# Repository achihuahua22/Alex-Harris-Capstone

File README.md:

# Alex Harris Capstone: Low Cost Device for Laboratory Equipment Integration
 _This project is a Raspberry Pi Hat that is intended to receive inputs from Self-Driving-Laboratory equipment and utilize the raspberry pi to publish device data onto the network.
This repository contains all of the schematics, documentation, and code necessary to build this device._

This project builds on an-ven’s [graspib](https://github.com/an-ven/graspib) project by adding more RS232 support and a UART breakout pin. 

It also utilizes the [Linux GPIB package](https://linux-gpib.sourceforge.io)

Currently, this device supports UART, RS232, and GPIB. 

If you want to make one yourself, the files are [here](capstone_cad_rev4)

## Introduction
This project is a Raspberry Pi Hat that is intended to 
improve self driving lab connectivity and modularity 
by allowing researchers to integrate multiple lab 
devices into their networks. I worked with Dr. Taylor 
Sparks' self-driving laboratory (SDL) to develop a 
device to more easily network with lab equipment. 
A self-driving laboratory is a laboratory where
everything from specimen handling, experiments, 
and decision making is fully automated to 
accelerate research [1]. This device intends to be an 
easy-to-use device for networking and save 
researchers money. To make a device “easy to use” I 
wanted to work with hardware that researchers are 
familiar with. This led to me choosing to design a 
board that attaches to a Raspberry Pi. 
I chose to use a Raspberry Pi based solution
because of its prevalence in the research space. 
Many pieces of university research level lab 
equipment have very little interconnection due to 
the age of the device or the type of communication 
protocol. Another issue is that products can use 
proprietary connection methods, which makes the 
task of developing an interconnected SDL very 
difficult [2]. I wanted to develop a device that can 
put data collected by lab equipment onto the 
network using a Raspberry Pi and a circuit board 
that sits on top of the Pi to handle the 
communications.

## Design
### Methods
I began with researching similar solutions to this 
problem, and the two options were a series of adapter 
dongles, or a device that interfaces with a single board 
computer to allow for communication. I chose this 
method as it would be easiest for the end user to have a 
single device that handles lab equipment connectivity.
I started by purchasing pre-built adapter components 
and build a breadboard analog of the final device. This 
device consisted of RS232 adapters and a serial 
expansion board for a Raspberry Pi. With this, I was able 
to test the idea of sending device data over the network 
using ROS and the python socket library.

### Results
I designed a circuit board that could serve as an add on 
that connected to the Raspberry Pi’s GPIO port. To 
expand the capability of the device, a GPIB connection
was added, taking advantage of the open-source Linux 
GPIB package [3]. GPIB is a very common protocol with 
adapters often costing hundreds of dollars.
The board was manufactured by JLCPCB, hand 
assembled, revised, and tested thoroughly. A GitHub 
repository was maintained throughout the project 
detailing hardware and software setup instructions.
The low-cost goal was achieved with the total cost being 
around $40 for the entire device excluding shipping

### Conclusions
Improvements of the Linux GPIB library are needed to 
facilitate easy setup of hardware and improved 
compatibility with the IEEE-488 standard.
Future works should expand on the software for using 
the Raspberry Pi to communicate over the local 
network. Possibly a user interface to improve ease of 
use
Future works should also investigate more permanent, 
universal communication protocols to improve 
laboratory equipment integration.

### Communication Protocols
While there are many communication protocols used in laboratory equipment, a few come up most often when looking at the back of devices in labs around my university. Some of these include:

1. RS232
2. CAN (CAN-FD, etc.)
3. GPIB
4. USB
5. UART
6. HPIB
7. Ethernet

Obviously, it is not possible to develop a device to encompass every existing communication protocol, so I chose three that were most necessary to our SDL and were most feasible with the constraint of a Raspberry Pi powered device. The three protocols I chose were RS232, UART, and GPIB. I chose each of these for the following reasons:
#### _UART_
I chose UART because of its prevalence in open-source projects such as the OpenTrickler, a powder dispensing device that we are using in our SDL. UART is also a simple protocol to implement as it only requires four pins: 3v3, TX, RX, and GND. The end user can configure the Baud rate, parity or stop bits in software. I believe that including this communication allows for other SDLs to integrate their own custom devices and not have to design for network capabilities if they choose to use my device. 
#### _RS232_
I chose RS232 because it was very prevalent in older equipment in our lab such as the Fischer Scientific Analytical Scale, and some open-source devices such as the OpenRAMAN, a laser spectroscopy device for materials classification. While RS232 is an old communication protocol, it is still useful for simple communication of commands. 
#### _GPIB_
Lastly, I chose GPIB because it was also extremely prevalent in many types of laboratory equipment such as multimeters, spectrum analyzers, and other devices. The issue that many laboratories face with GPIB enabled devices is that adapters such as GPIB to USB can cost more than $1,000 and can only communicate with proprietary software. This can render perfectly usable lab equipment almost completely useless in terms of automation or remote data collection.

The following are protocols I didn't choose, future works could consider adding them.

#### _CAN_
I didn’t choose CAN or any of its variants (CAN, CAN-FD, CAN-XL) because it has too many variants to effectively develop a multipurpose product that could encompass of CAN. The differential pair nature of CAN also makes it difficult to develop for.
#### _USB_
I didn’t choose USB because of its complication with drivers, enumeration, host/peripheral, and all the headaches that come with that. In addition to this, a Raspberry Pi does not have the same driver setup as a normal computer which makes implementation difficult when this problem can be solved with a computer and a USB hub.
#### _HPIB_
I didn’t choose HPIB because of the general nature of GPIB (General Purpose Interface Bus) and how HPIB is limited to Hewlett-Packard devices, and that does not make sense with the intent of this project.
#### _Ethernet_
I didn’t choose Ethernet because it also defeats the purpose of this project. The Raspberry Pi used for this project has Ethernet connection capabilities, allowing me to develop a device that just handles the communications between the laboratory equipment and the Pi, reducing cost and complexity.

## Device Assembly
### PCB Manufacturing
At the time of writing, JLCPCB is a very good option for low cost PCB manufacturing. You can get 5 boards for roughly $4 not including shipping. All you need to do is zip these [Gerber Files](https://github.com/achihuahua22/Alex-Harris-Capstone/tree/main/capstone_rev4_gerbers), go to JLCPCB.com, click "upload gerbers" and choose the zipped file. Everything else should populate automatically. You don't need to do any configuration besides choosing the "Lead Free HASL" for a lead free surface finish on the pcb. Feel free to order a stencil as it might make surface mount soldering easier, not required though.

### Parts
Here is the [BOM](https://github.com/achihuahua22/Alex-Harris-Capstone/blob/main/bill_of_materials/senior_capstone_bom_rev4.csv) for the pcb components
   - Unfortunately, all of the components except for item 15 (SN75161BDW) can be purchased from Digikey, the remaining component can be purchased from Mouser
   - In addition, I would recommend M2.5 standoffs to support the board on top of the raspberry pi
   - Solder paste and Heat Gun is recommended for the Surface Mount components as the Resistors, Capacitors, and LED's

### Building
I would recommend using solder paste and a heat gun for installing the small surface mount components such as the resistors, capacitors, crystal and LED's and installing the components in the following order:
1. Resistors (R1-R12)
2. Crystal Oscillator (Y1)
3. Capacitors (C1-C8)
4. LED's (D1-D7) (*pay attention to the orientation of the LED!*)
   - The open part of the rectangle is the anode, the closed part is the cathode
5. Integrated Circuits (U1-U4) (In order of 1 to 4 is easiest)
6. Connectors

It is not required to install the components in this order, but is is easier to install the smaller components first so you don't have to navigate around the large connectors or IC's.
   
## Setup
1. Setup fresh install of [raspberry pi os](https://www.raspberrypi.com/software/)
2. Configure your network, password, etc to your liking
3. Download Provided [files](https://github.com/achihuahua22/Alex-Harris-Capstone/blob/main/send_to_network.c) to send data to network
4. From [graspib documentation](https://github.com/an-ven/graspib/tree/main) : 

   Install build tools and dependencies
   - Build tools: ```$ sudo apt install build-essential autoconf automake libtool flex bison```
   - RPi kernel headers: ```$ sudo apt install raspberrypi-kernel-headers```
   - Python3 headers: ```$ sudo apt install python3-dev```

    Download linux-gpib source files
   - Get release archives (4.3.4 or later) from https://sourceforge.net/projects/linux-gpib/files
   - or get the latest source from https://sourceforge.net/p/linux-gpib/code/HEAD/tree/

   Build and install kernel drivers
   - Enter linux-gpib-kernel directory ```$ cd linux-gpib-src-dir/linux-gpib-kernel```
   - Build kernel module by running make ```$ make```
   - Install kernel module ```$ sudo make install```
   - Update kernel module list ```$ sudo depmod -a```
   - Load gpib_bitbang kernel module ```$ sudo modprobe gpib_bitbang```
   - Now there should be some gpib* devices in /dev
   - Make the module loads on boot by adding gpib_bitbang line to /etc/modules-load.d/modules.conf

   When Raspberry Pi OS kernel gets upgraded, linux-gpib kernel module also needs to be rebuilt and reinstalled. 
   Basically just repeat above make and make install steps when kernel gets upgraded

   Build and install user space tools
   - Enter linux-gpib-user directory: ```$ cd linux-gpib-src-dir/linux-gpib-user```
   - If building from svn checkout first run bootstrap script: $ ./bootstrap
   - Run configure script: ```$ ./configure (run $ ./configure --help to list additional options)```
   - Build user space tools by running make: $ make
   - Install user space tools: ```$ sudo make install```
   - Make sure that shared library directory (default: /usr/local/lib/) is listed in: /etc/ld.so.conf.d/
   - Then run: $ sudo ldconfig

   Configure GPIB interface
   - Open gpib.conf configuration file $ sudo nano /usr/local/etc/gpib.conf (default location)
   - Set board_type = "gpib_bitbang" and other relevant settings (for details refer to included gpib.conf file, linux-gpib documentetion and included template file linux-gpib-src-dir/linux-gpib-user/util/template/gpib.conf)
   - Run gpib_config so the driver reads the configuration file $ sudo gpib_config --minor 0
   - Make the last command execute on every startup using crontab entry:
   - Edit crontab for root user: ```$ sudo crontab -e```
   - Add line the following line to cron tab file: @reboot /usr/local/sbin/gpib_config --minor 0
   - Enable non root users to use GPIB interface without sudo
   - Add new gpib system group: ```$ sudo groupadd -r gpib```
   - Append your_user_name to gpib supplementary group: ```$ sudo usermod -a -G gpib your_user_name```
   - Create /etc/udev/rules.d/99-gpib.rules file and add line: SUBSYSTEM=="gpib_common", GROUP="gpib", MODE="0660"

Reboot system to apply changes (udevadm utility can also be used, but reboot is dead simple to remember)
Test by running ibtest without sudo

5. Run and do the following to enable the I2C interface:
   - Open a terminal and run ```sudo raspi-config```
   - Select "Interface Options"
   - Select "P5 I2C"
   - It will prompt you with "Would you like the ARM I2C interface to be enabled?" *select yes*
   - Then it will prompt you to reboot *select yes*
   - After reboot, open another terminal and run ```sudo apt-get update``` and ```sudo apt-get install -y python3-smbus i2c-tools```
   - Finally shut down the raspberry pi with ```sudo halt```
   - Wait 10 seconds unplug power and restart
6. Run the following in the raspberry pi os terminal to configure serial and socket:
   
   - Update package list ```sudo apt update```
   - Install socket ```python3 -m pip install socket```
   - Install pySerial ```python3 -m pip install pyserial```
   - Install WiringPi ```sudo apt install wiringpi```
   - Install build tools ```sudo apt install build-essential```

7. See following [instructions](https://github.com/an-ven/graspib/tree/main) from grasPIB repository to configure the raspberry pi for GPIB
8. Configure Baud rate, IP, and I2C addresses in code

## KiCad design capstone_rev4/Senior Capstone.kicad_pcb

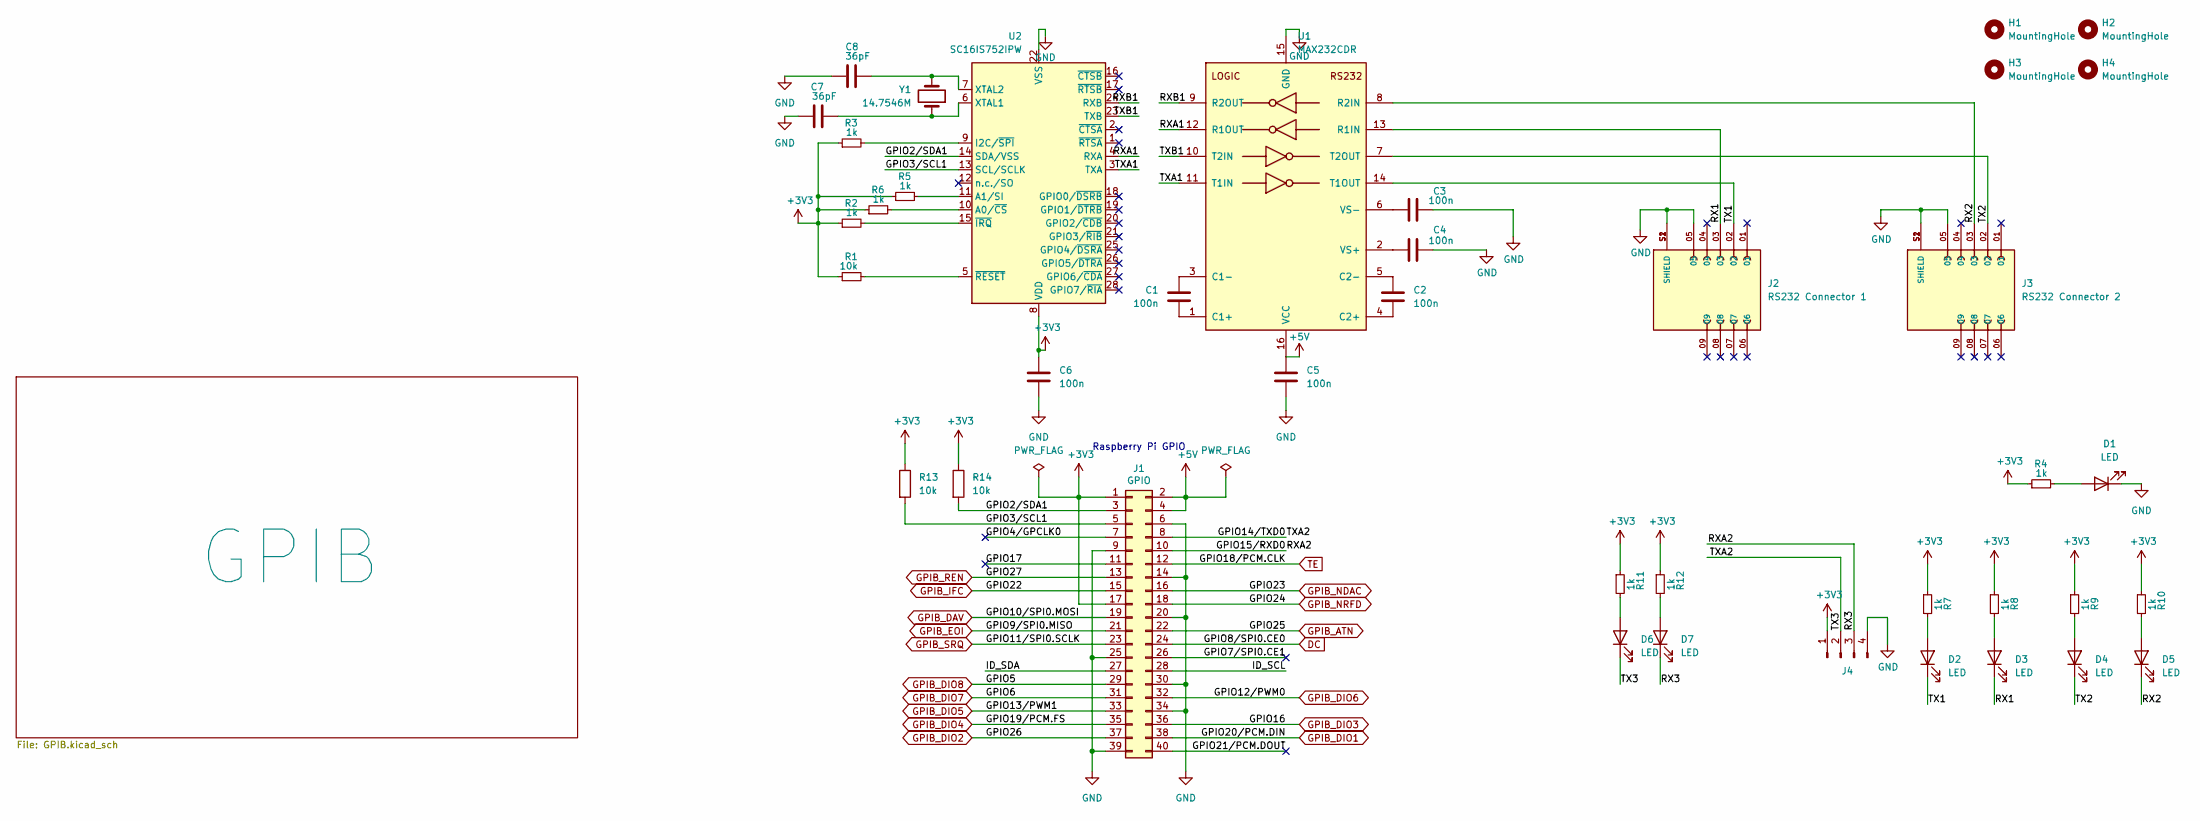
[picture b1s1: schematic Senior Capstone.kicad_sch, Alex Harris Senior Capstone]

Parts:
C1, C2, C3, C4, C5, C6: 100n; C_0805_2012Metric
C7, C8: 36pF; C_0805_2012Metric_Pad1.18x1.45mm_HandSolder
D1, D2, D3, D4, D5, D6, D7: LED; LED_1206_3216Metric_Pad1.42x1.75mm_HandSolder
H1, H2, H3, H4: MountingHole; MountingHole_2.7mm_M2.5_DIN965_Pad_TopBottom
J1: GPIO; PinSocket_2x20_P2.54mm_Vertical
J2: RS232 Connector 1; AMPHENOL_L77SDE09SA4CH3FC309; PARTREV 1
J3: RS232 Connector 2; AMPHENOL_L77SDE09SA4CH3FC309; PARTREV 1
J4: Conn_01x04_Pin; PinHeader_1x04_P2.54mm_Vertical
R1, R13, R14: 10k; R_0805_2012Metric_Pad1.20x1.40mm_HandSolder
R2, R3, R4, R5, R6, R7, R8, R9, R10, R11, R12: 1k; R_0805_2012Metric_Pad1.20x1.40mm_HandSolder
U1: MAX232CDR; SOIC-16_3.9x9.9mm_P1.27mm
U2: SC16IS752IPW; TSSOP-28_4.4x9.7mm_P0.65mm
Y1: 14.7546M; XTAL_405C35B14M74560

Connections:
+3V3: C6.1, J1.1, J1.17, J4.1, R1.1, R2.1, R3.1, R4.1, R5.1, R6.1, R7.1, R8.1, R9.1, R10.1, R11.1, R12.1, R13.1, R14.1, U2.8 (VDD)
+5V: C5.1, J1.2, J1.4, U1.16 (VCC); also elsewhere on the board
/GPIO2/SDA1: J1.3, R14.2, U2.14 (SDA/VSS)
/GPIO3/SCL1: J1.5, R13.2, U2.13 (SCL/SCLK)
/GPIO4/GPCLK0: J1.7
/GPIO7/SPI0.CE1: J1.26
/GPIO14/TXD0: D6.1 (K), J1.8, J4.2
/GPIO15/RXD0: D7.1 (K), J1.10, J4.3
/GPIO17: J1.11
/GPIO21/PCM.DOUT: J1.40
/ID_SCL: J1.28
/ID_SDA: J1.27
/RX1: D3.1 (K), J2.03, U1.13 (R1IN)
/RX2: D5.1 (K), J3.03, U1.8 (R2IN)
/RXA1: U1.12 (R1OUT), U2.4 (RXA)
/RXB1: U1.9 (R2OUT), U2.24 (RXB)
/TX1: D2.1 (K), J2.02, U1.14 (T1OUT)
/TX2: D4.1 (K), J3.02, U1.7 (T2OUT)
/TXA1: U1.11 (T1IN), U2.3 (TXA)
/TXB1: U1.10 (T2IN), U2.23 (TXB)
DC: J1.24; also elsewhere on the board
GND: C3.2, C4.2, C5.2, C6.2, C7.2, C8.2, D1.1 (K), J1.6, J1.9, J1.14, J1.20, J1.25, J1.30, J1.34, J1.39, J2.05, J2.S1 (SHIELD), J2.S2 (SHIELD), J3.05, J3.S1 (SHIELD), J3.S2 (SHIELD), J4.4, U1.15 (GND), U2.22 (VSS); also elsewhere on the board
GPIB_ATN: J1.22; also elsewhere on the board
GPIB_DAV: J1.19; also elsewhere on the board
GPIB_DIO1: J1.38; also elsewhere on the board
GPIB_DIO2: J1.37; also elsewhere on the board
GPIB_DIO3: J1.36; also elsewhere on the board
GPIB_DIO4: J1.35; also elsewhere on the board
GPIB_DIO5: J1.33; also elsewhere on the board
GPIB_DIO6: J1.32; also elsewhere on the board
GPIB_DIO7: J1.31; also elsewhere on the board
GPIB_DIO8: J1.29; also elsewhere on the board
GPIB_EOI: J1.21; also elsewhere on the board
GPIB_IFC: J1.15; also elsewhere on the board
GPIB_NDAC: J1.16; also elsewhere on the board
GPIB_NRFD: J1.18; also elsewhere on the board
GPIB_REN: J1.13; also elsewhere on the board
GPIB_SRQ: J1.23; also elsewhere on the board
unnamed: D1.2 (A), R4.2
unnamed: D2.2 (A), R7.2
unnamed: D3.2 (A), R8.2
unnamed: D4.2 (A), R9.2
unnamed: D5.2 (A), R10.2
unnamed: D6.2 (A), R11.2
unnamed: D7.2 (A), R12.2
unnamed: C1.2, U1.1 (C1+)
unnamed: C1.1, U1.3 (C1-)
unnamed: C2.2, U1.4 (C2+)
unnamed: C2.1, U1.5 (C2-)
unnamed: C4.1, U1.2 (VS+)
unnamed: C3.1, U1.6 (VS-)
unnamed: R6.2, U2.10 (A0/~CS)
unnamed: R5.2, U2.11 (A1/SI)
unnamed: R3.2, U2.9 (I2C/~SPI)
unnamed: C7.1, U2.6 (XTAL1), Y1.1
unnamed: C8.1, U2.7 (XTAL2), Y1.2
unnamed: R2.2, U2.15 (~IRQ)
unnamed: R1.2, U2.5 (~RESET)
TE: J1.12; also elsewhere on the board

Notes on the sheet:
Raspberry Pi GPIO

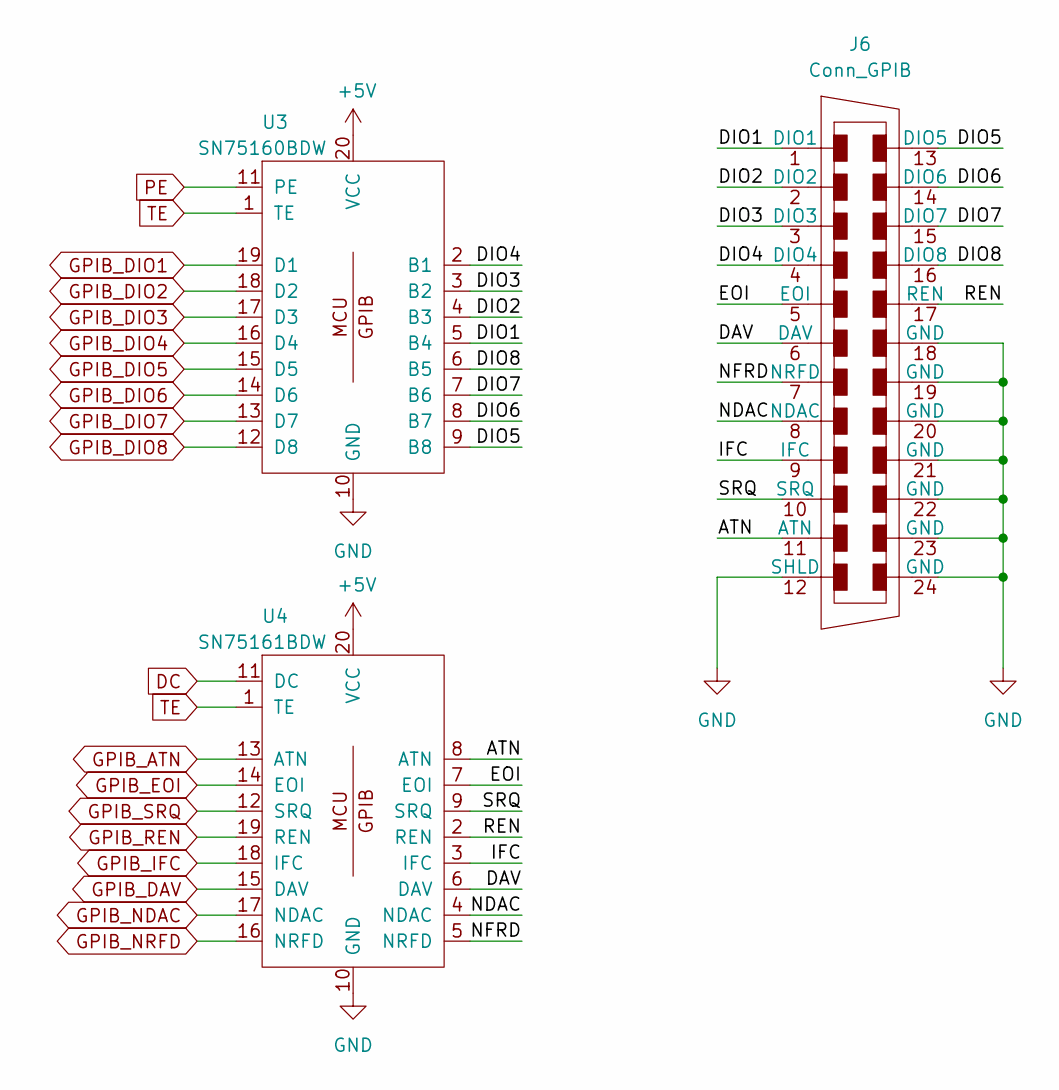
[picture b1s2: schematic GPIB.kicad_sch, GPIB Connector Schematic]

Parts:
J6: Conn_GPIB; CONN_112-024-113R001_NRC
U3: SN75160BDW; SOIC127P1030X265-20N
U4: SN75161BDW; SOIC127P1030X265-20N

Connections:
+5V: U3.20 (VCC), U4.20 (VCC); also elsewhere on the board
/GPIB/ATN: J6.11 (ATN), U4.8 (ATN)
/GPIB/DAV: J6.6 (DAV), U4.6 (DAV)
/GPIB/DIO1: J6.1 (DIO1), U3.5 (B4)
/GPIB/DIO2: J6.2 (DIO2), U3.4 (B3)
/GPIB/DIO3: J6.3 (DIO3), U3.3 (B2)
/GPIB/DIO4: J6.4 (DIO4), U3.2 (B1)
/GPIB/DIO5: J6.13 (DIO5), U3.9 (B8)
/GPIB/DIO6: J6.14 (DIO6), U3.8 (B7)
/GPIB/DIO7: J6.15 (DIO7), U3.7 (B6)
/GPIB/DIO8: J6.16 (DIO8), U3.6 (B5)
/GPIB/EOI: J6.5 (EOI), U4.7 (EOI)
/GPIB/IFC: J6.9 (IFC), U4.3 (IFC)
/GPIB/NDAC: J6.8 (NDAC), U4.4 (NDAC)
/GPIB/NFRD: J6.7 (NRFD), U4.5 (NRFD)
/GPIB/REN: J6.17 (REN), U4.2 (REN)
/GPIB/SRQ: J6.10 (SRQ), U4.9 (SRQ)
DC: U4.11 (DC); also elsewhere on the board
GND: J6.12 (SHLD), J6.18 (GND), J6.19 (GND), J6.20 (GND), J6.21 (GND), J6.22 (GND), J6.23 (GND), J6.24 (GND), U3.10 (GND), U4.10 (GND); also elsewhere on the board
GPIB_ATN: U4.13 (ATN); also elsewhere on the board
GPIB_DAV: U4.15 (DAV); also elsewhere on the board
GPIB_DIO1: U3.19 (D1); also elsewhere on the board
GPIB_DIO2: U3.18 (D2); also elsewhere on the board
GPIB_DIO3: U3.17 (D3); also elsewhere on the board
GPIB_DIO4: U3.16 (D4); also elsewhere on the board
GPIB_DIO5: U3.15 (D5); also elsewhere on the board
GPIB_DIO6: U3.14 (D6); also elsewhere on the board
GPIB_DIO7: U3.13 (D7); also elsewhere on the board
GPIB_DIO8: U3.12 (D8); also elsewhere on the board
GPIB_EOI: U4.14 (EOI); also elsewhere on the board
GPIB_IFC: U4.18 (IFC); also elsewhere on the board
GPIB_NDAC: U4.17 (NDAC); also elsewhere on the board
GPIB_NRFD: U4.16 (NRFD); also elsewhere on the board
GPIB_REN: U4.19 (REN); also elsewhere on the board
GPIB_SRQ: U4.12 (SRQ); also elsewhere on the board
PE: U3.11 (PE)
TE: U3.1 (TE), U4.1 (TE); also elsewhere on the board

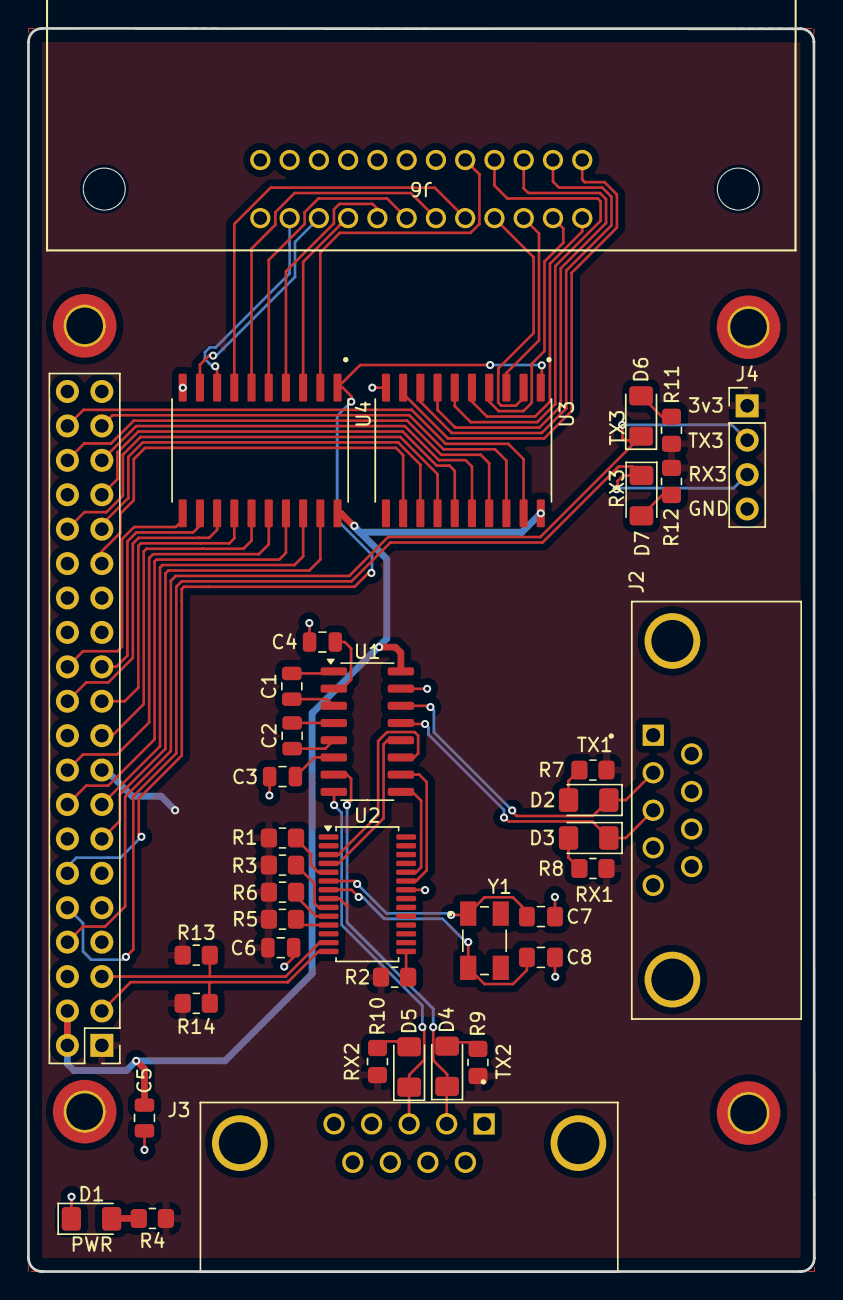
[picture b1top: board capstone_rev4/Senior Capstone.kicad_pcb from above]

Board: 2 copper layers, 58.0 x 91.8 mm, 43 parts (0 on the bottom side), 69 nets.

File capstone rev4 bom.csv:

Index,Manufacturer Part Number,Manufacturer Name,Description,References,Requested Quantity 1,Pack Quantity 1,Pack Type 1,Digi-Key Part Number 1,Unit Price 1,Extended Price 1,Minimum Order Quantity 1,Datasheet,Product Notes
1,22284040,Molex,CONN HEADER VERT 4POS 2.54MM,J4,1,1,Bulk,WM50014-04-ND,0.3,$0.30 ,1,https://www.molex.com/pdm_docs/sd/022284040_sd.pdf,
2,RC0805FR-071KL,YAGEO,RES 1K OHM 1% 1/8W 0805,"R2, R3, R4, R5, R6, R7, R8, R9, R10, R11, R12",11,11,Cut Tape (CT),311-1.00KCRCT-ND,0.012,$0.13 ,1,https://www.yageo.com/upload/media/product/products/datashee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,
3,08055C104J4T2A,KYOCERA AVX,CAP CER 0.1UF 50V X7R 0805,C1-C6,7,7,Cut Tape (CT),478-KAM21BR71H104JTCT-ND,0.18,$1.26 ,1,https://datasheets.kyocera-avx.com/AutoMLCC.pdf,
4,"SC16IS752IPW,112",NXP USA Inc.,IC UART DUAL 12C/SPI 28TSSOP,U2,1,1,Tube,568-4016-5-ND,4.48,$4.48 ,1,https://www.nxp.com/docs/en/data-sheet/SC16IS752_SC16IS762.pdf,
5,SN75160BDW,Texas Instruments,IC TRANSCEIVER HALF 8/8 20SOIC,U3,1,1,Tube,296-6844-5-ND,3.39,$3.39 ,1,https://www.ti.com/general/docs/suppproductinfo.tsp?distId=1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,
6,CIB24SRA,L-com,CONNECTOR GPIB R/A FEMALE,J5,1,1,Bag,5073-CIB24SRA-ND,17.1,$17.10 ,1,https://www.l-com.com/images/downloadables/2D/CIB24SRA_2D.pdf,
7,PRT-16764,SparkFun Electronics,EXTENDED GPIO FEMALE HEADER - 2X,J1,1,1,Bulk,1568-PRT-16764-ND,2.25,$2.25 ,1,https://cdn.sparkfun.com/assets/0/8/d/b/2/DS-16764-2_X_20_Pi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,
8,405C35B14M74560,CTS-Frequency Controls,CRYSTAL 14.7456MHZ 13PF SMD,Y1,1,1,Cut Tape (CT),CTX644CT-ND,0.84,$0.84 ,1,https://www.ctscorp.com/Files/DataSheets/Passives/FCP/Crysta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,
9,LD09P13A4GX00LF,Amphenol ICC (FCI),CONN D-SUB PLUG 9POS R/A SOLDER,"J2,J3",2,2,Tray,609-5183-ND,1.23,$2.46 ,1,https://cdn.amphenol-cs.com/media/wysiwyg/files/documentatio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,
10,CC0805JRNPO9BN360,YAGEO,CAP CER 36PF 50V C0G/NPO 0805,"C7,C8",2,2,Cut Tape (CT),311-4236-1-ND,0.12,$0.24 ,1,https://www.yageo.com/en/Chart/Download/pdf/CC0805JRNPO9BN360,
11,MAX3232CDR,Texas Instruments,IC TRANSCEIVER FULL 2/2 16SOIC,U1,1,1,Cut Tape (CT),296-13094-1-ND,0.98,$0.98 ,1,https://www.ti.com/lit/ds/symlink/max3232.pdf,
12,LTST-C150KRKT,Lite-On Inc.,LED RED CLEAR 1206 SMD,D1,1,1,Cut Tape (CT),160-1405-1-ND,0.18,$0.18 ,1,https://optoelectronics.liteon.com/upload/download/DS-22-99-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,
13,LTST-C150GKT,Lite-On Inc.,LED GREEN CLEAR 1206 SMD,"D2, D3, D4, D5, D6, D7",6,6,Cut Tape (CT),160-1169-1-ND,0.17,$1.02 ,1,https://optoelectronics.liteon.com/upload/download/DS-22-98-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,
14,RMCF0805FT10K0,Stackpole Electronics Inc,RES 10K OHM 1% 1/8W 0805,"R1,R13,R14",4,4,Cut Tape (CT),RMCF0805FT10K0CT-ND,0.1,$0.40 ,1,https://www.seielect.com/catalog/sei-rmcf_rmcp.pdf,
15,SN75161BDW,296-6846-5-ND,IC TRANSCEIVER HALF 8/8 20SOIC,U4,1,,,,,,,,
,,,,,,,,,,,,,
,,,,,,,,,,,,,
,,,,,,,,,,,,,
,,,,,,,,,,,,,
,,,,,,,,,,,,,
,,,,,,,,,,,,,
,,,,,,,,,,,,,
,,,,,,,,,,,,,
,,,,,,,,,,,,,
,,,,,,,,,,,,,
,,,,,,,,,,,,,
,,,,,,,,,,,,,
,,,,,,,,,,,,,
,,,,,,,,,,,,,
,,,,,,,,,,,,,
,,,,,,,,,,,,,
,,,,,,,,,,,,,
,,,,,,$35.81 ,,,,,,,

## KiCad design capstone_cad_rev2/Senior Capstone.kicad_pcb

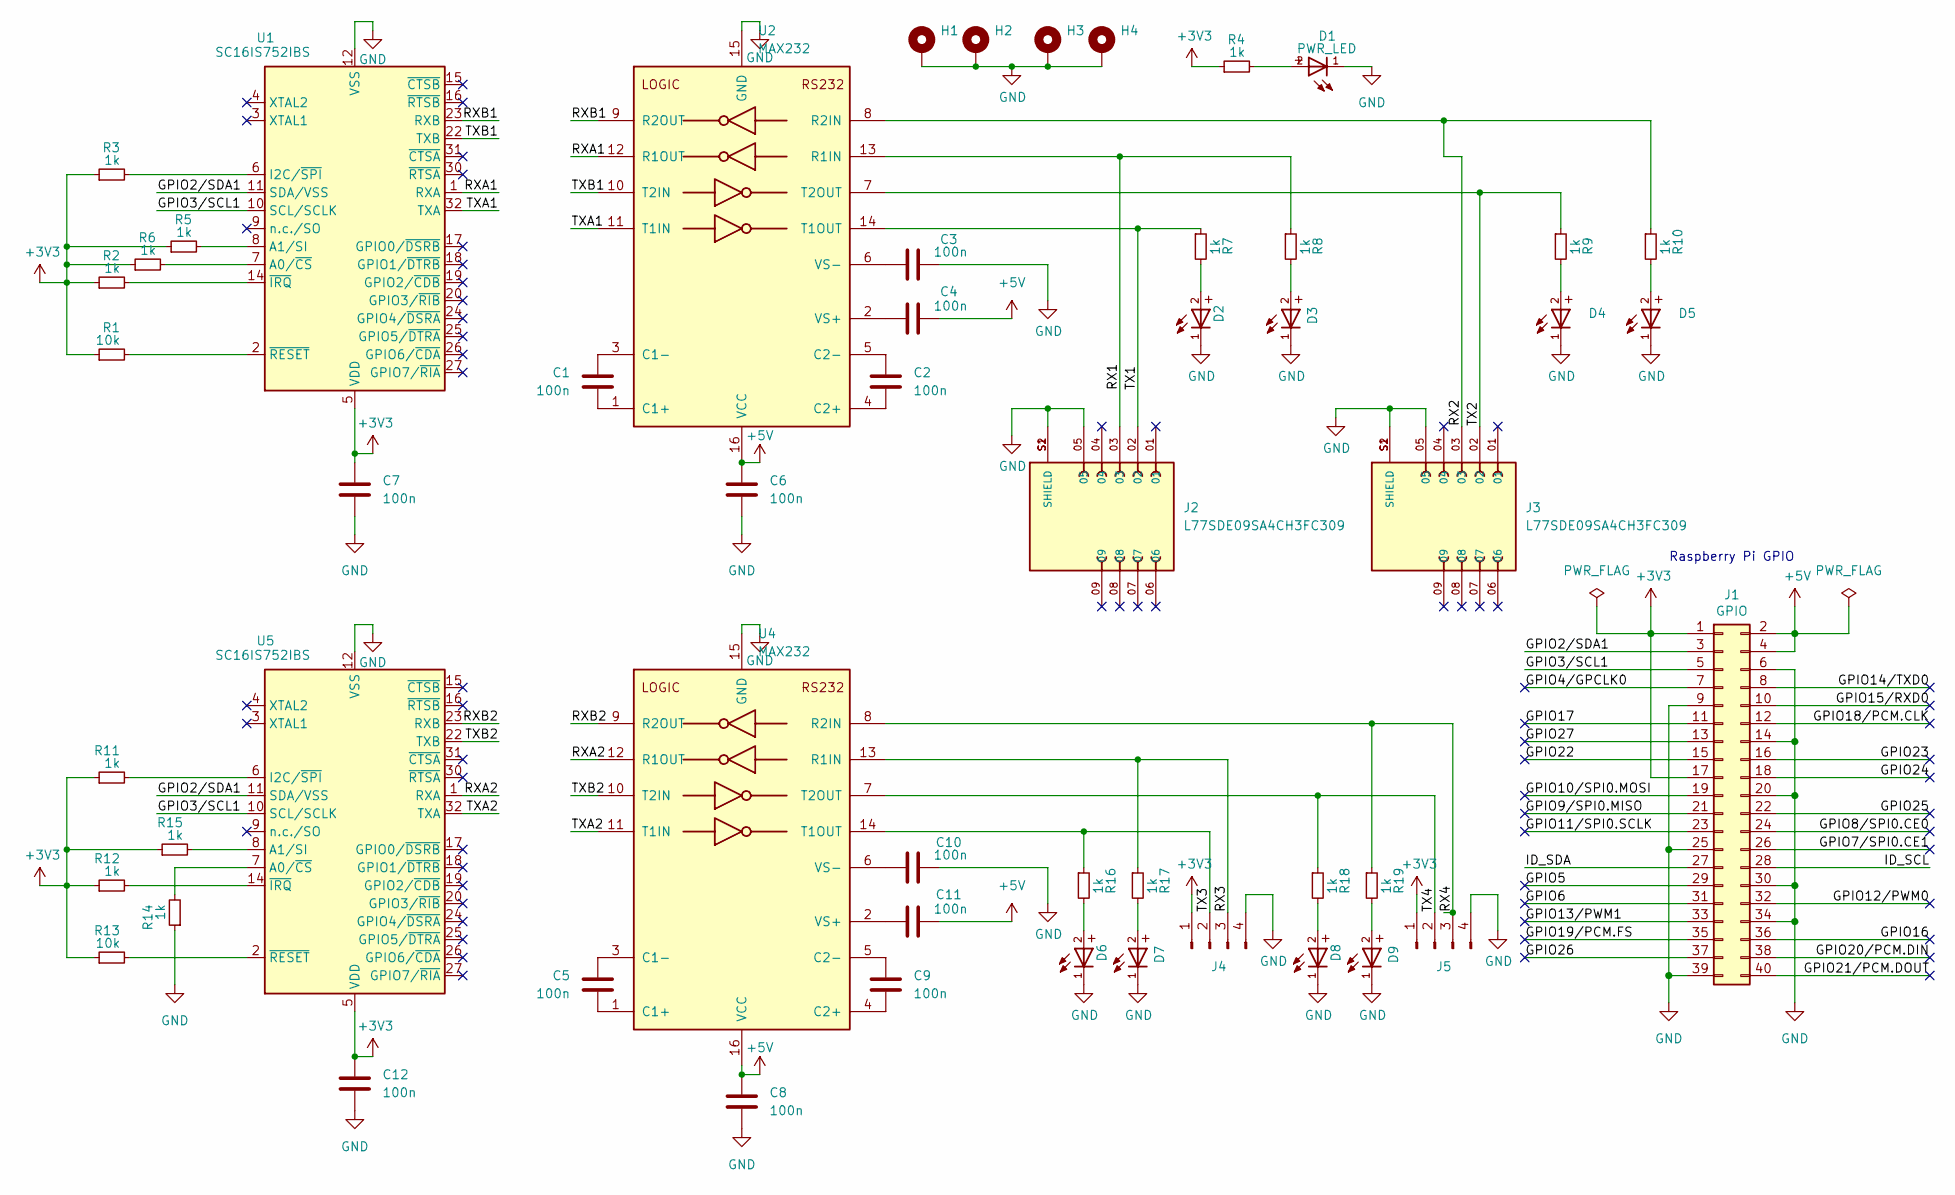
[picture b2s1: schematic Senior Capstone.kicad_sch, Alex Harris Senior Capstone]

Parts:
C1, C2, C3, C4, C5, C6, C7, C8, C9, C10, C11, C12: 100n; C_0805_2012Metric
D1: PWR_LED; WL-SMCW_0603
D2, D3, D4, D5, D6, D7, D8, D9: WL-SMCW_0603
H1, H2, H3, H4: MountingHole_Pad; MountingHole_2.2mm_M2_ISO7380_Pad_TopBottom
J1: GPIO; PinSocket_2x20_P2.54mm_Vertical
J2, J3: L77SDE09SA4CH3FC309; AMPHENOL_L77SDE09SA4CH3FC309; PARTREV 1
J4, J5: Conn_01x04_Pin; PinHeader_1x04_P2.54mm_Vertical
R1, R13: 10k; R_0805_2012Metric_Pad1.20x1.40mm_HandSolder
R2, R3, R4, R5, R6, R7, R8, R9, R10, R11, R12, R14, R15, R16, R17, R18, R19: 1k; R_0805_2012Metric_Pad1.20x1.40mm_HandSolder
U1, U5: SC16IS752IBS; VQFN-32-1EP_5x5mm_P0.5mm_EP3.1x3.1mm
U2, U4: MAX232; TSSOP-16_4.4x5mm_P0.65mm

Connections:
+3V3: C7.1, C12.1, J1.1, J1.17, J4.1, J5.1, R1.1, R2.1, R3.1, R4.1, R5.1, R6.1, R11.1, R12.1, R13.1, R15.1, U1.5 (VDD), U1.13 (VDD), U1.28 (VDD), U5.5 (VDD), U5.13 (VDD), U5.28 (VDD)
+5V: C4.2, C6.1, C8.1, C11.2, J1.2, J1.4, U2.16 (VCC), U4.16 (VCC)
/GPIO2/SDA1: J1.3, U1.11 (SDA/VSS), U5.11 (SDA/VSS)
/GPIO3/SCL1: J1.5, U1.10 (SCL/SCLK), U5.10 (SCL/SCLK)
/GPIO4/GPCLK0: J1.7
/GPIO5: J1.29
/GPIO6: J1.31
/GPIO7/SPI0.CE1: J1.26
/GPIO8/SPI0.CE0: J1.24
/GPIO9/SPI0.MISO: J1.21
/GPIO10/SPI0.MOSI: J1.19
/GPIO11/SPI0.SCLK: J1.23
/GPIO12/PWM0: J1.32
/GPIO13/PWM1: J1.33
/GPIO14/TXD0: J1.8
/GPIO15/RXD0: J1.10
/GPIO16: J1.36
/GPIO17: J1.11
/GPIO18/PCM.CLK: J1.12
/GPIO19/PCM.FS: J1.35
/GPIO20/PCM.DIN: J1.38
/GPIO21/PCM.DOUT: J1.40
/GPIO22: J1.15
/GPIO23: J1.16
/GPIO24: J1.18
/GPIO25: J1.22
/GPIO26: J1.37
/GPIO27: J1.13
/ID_SCL: J1.28
/ID_SDA: J1.27
/RX1: J2.03, R8.1, U2.13 (R1IN)
/RX2: J3.03, R10.1, U2.8 (R2IN)
/RX3: J4.3, R17.1, U4.13 (R1IN)
/RX4: J5.3, R19.1, U4.8 (R2IN)
/RXA1: U1.1 (RXA), U2.12 (R1OUT)
/RXA2: U4.12 (R1OUT), U5.1 (RXA)
/RXB1: U1.23 (RXB), U2.9 (R2OUT)
/RXB2: U4.9 (R2OUT), U5.23 (RXB)
/TX1: J2.02, R7.1, U2.14 (T1OUT)
/TX2: J3.02, R9.1, U2.7 (T2OUT)
/TX3: J4.2, R16.1, U4.14 (T1OUT)
/TX4: J5.2, R18.1, U4.7 (T2OUT)
/TXA1: U1.32 (TXA), U2.11 (T1IN)
/TXA2: U4.11 (T1IN), U5.32 (TXA)
/TXB1: U1.22 (TXB), U2.10 (T2IN)
/TXB2: U4.10 (T2IN), U5.22 (TXB)
GND: C3.2, C6.2, C7.2, C8.2, C10.2, C12.2, D1.1, D2.1, D3.1, D4.1, D5.1, D6.1, D7.1, D8.1, D9.1, H1.1, H2.1, H3.1, H4.1, J1.6, J1.9, J1.14, J1.20, J1.25, J1.30, J1.34, J1.39, J2.05, J2.S1 (SHIELD), J2.S2 (SHIELD), J3.05, J3.S1 (SHIELD), J3.S2 (SHIELD), J4.4, J5.4, R14.1, U1.12 (VSS), U1.21 (VSS), U1.29 (VSS), U1.33 (VSS), U2.15 (GND), U4.15 (GND), U5.12 (VSS), U5.21 (VSS), U5.29 (VSS), U5.33 (VSS)
unnamed: D1.2, R4.2
unnamed: D2.2, R7.2
unnamed: D3.2, R8.2
unnamed: D4.2, R9.2
unnamed: D5.2, R10.2
unnamed: D6.2, R16.2
unnamed: D7.2, R17.2
unnamed: D8.2, R18.2
unnamed: D9.2, R19.2
unnamed: R6.2, U1.7 (A0/~CS)
unnamed: R5.2, U1.8 (A1/SI)
unnamed: R3.2, U1.6 (I2C/~SPI)
unnamed: R2.2, U1.14 (~IRQ)
unnamed: R1.2, U1.2 (~RESET)
unnamed: C1.2, U2.1 (C1+)
unnamed: C1.1, U2.3 (C1-)
unnamed: C2.2, U2.4 (C2+)
unnamed: C2.1, U2.5 (C2-)
unnamed: C4.1, U2.2 (VS+)
unnamed: C3.1, U2.6 (VS-)
unnamed: C5.2, U4.1 (C1+)
unnamed: C5.1, U4.3 (C1-)
unnamed: C9.2, U4.4 (C2+)
unnamed: C9.1, U4.5 (C2-)
unnamed: C11.1, U4.2 (VS+)
unnamed: C10.1, U4.6 (VS-)
unnamed: R14.2, U5.7 (A0/~CS)
unnamed: R15.2, U5.8 (A1/SI)
unnamed: R11.2, U5.6 (I2C/~SPI)
unnamed: R12.2, U5.14 (~IRQ)
unnamed: R13.2, U5.2 (~RESET)

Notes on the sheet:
Raspberry Pi GPIO

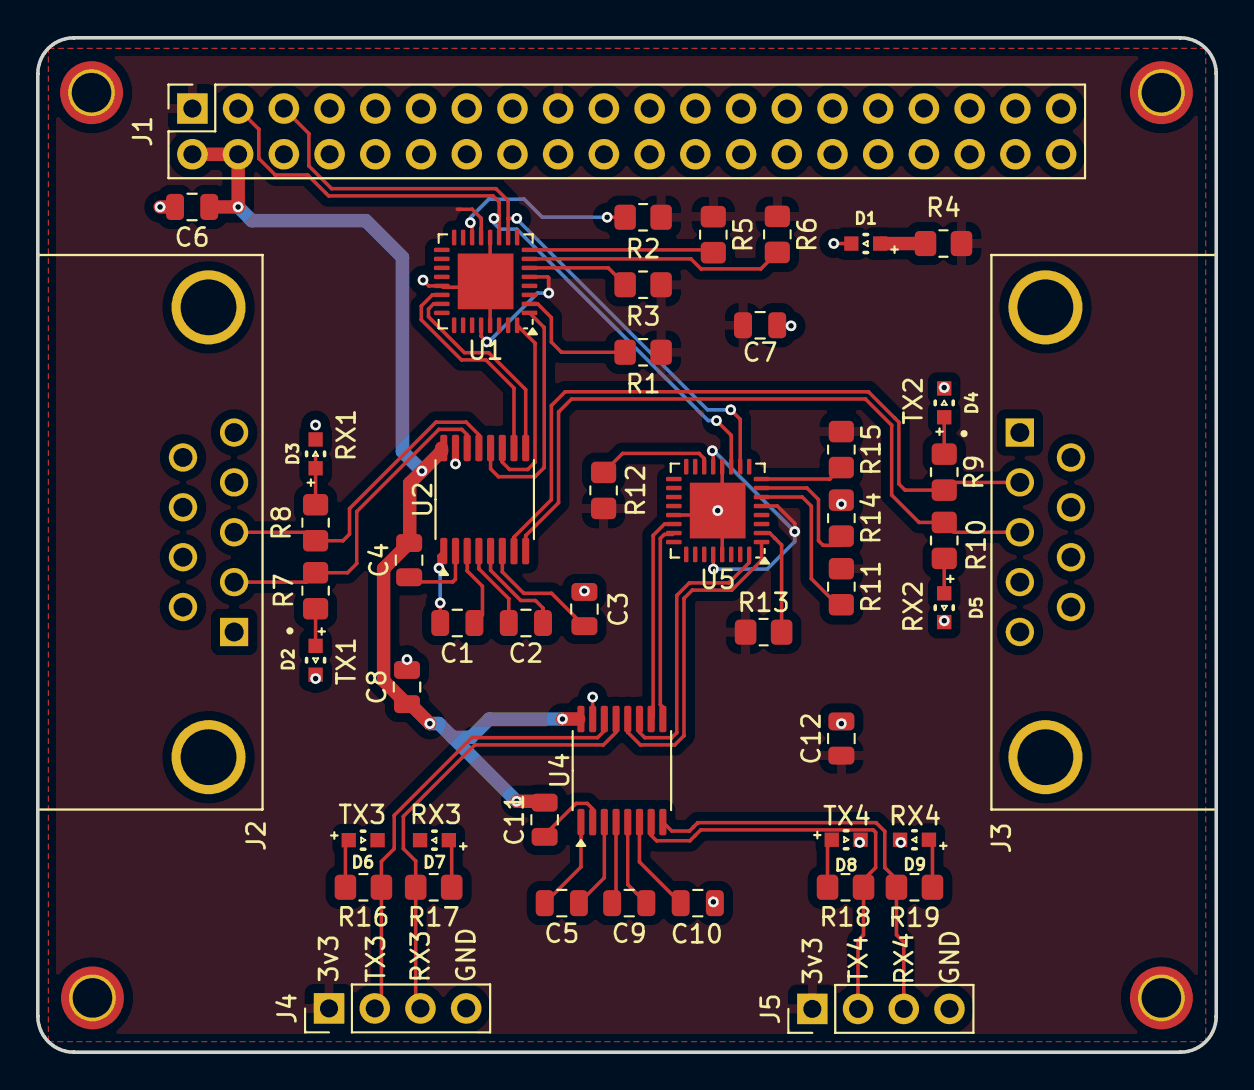
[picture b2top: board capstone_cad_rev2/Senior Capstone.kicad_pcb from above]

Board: 2 copper layers, 65.5 x 56.4 mm, 53 parts (0 on the bottom side), 52 nets.

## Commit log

2024-11-20 test push
2024-11-20 import pyserial
2024-11-20 import serial :)
2024-11-20 added serial open
2024-11-20 Serial print loop
2024-11-24 test
2024-11-24 imported spi and roslibpy packages
2024-11-24 fix?
2024-11-24 rospy
2024-11-24 i2c sleep
2024-11-24 rostest
2024-11-25 rostest2
2024-11-25 print only
2024-11-25 tryros
2024-11-25 python3
2024-11-25 comment out imports
2024-11-25 successful ros node creation
2025-03-03 rev2 and rev3 bom
2025-03-03 replace rev2 bom
2025-03-08 capstone rev3 cad files and gerbers
2025-03-08 rename files
2025-03-08 rename rev2
2025-03-08 move boms into folder
2025-03-11 add send to network code
2025-03-11 Update README.md with setup instructions
2025-03-11 3d model screenshot upload
2025-04-07 rev4 files
2025-04-07 rev4 bom
2025-04-07 move rev4 bom
2025-04-07 capstone rev4 gerbers
2025-04-25 update intructions
2025-04-25 fix code md issue
2025-04-25 formatting
2025-04-25 format
2025-04-25 tabbing
2025-04-25 form
2025-04-25 revised intro,methods,results,conclusion
2025-04-25 add sources
2025-04-25 format source
